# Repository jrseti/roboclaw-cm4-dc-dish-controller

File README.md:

# roboclaw-cm4-dc-dish-controller

A radio astronomy dish controller: a carrier board for a Raspberry Pi Compute
Module 4 (CM4) that commands a Basicmicro **RoboClaw 2x15A OEM** brushed DC motor
controller to drive the dish's azimuth and elevation motors. The board runs from a
12.8 V LiFePO4 battery that can be charged from a solar panel.

The goal is a self-contained observing system that points the dish, gathers data
and stores it for later retrieval and analysis. An SDR, such as an Airspy R2,
plugs into one USB port and an SSD into the other. The CM4 stores the samples
either raw or integrated. Both share one USB 2.0 link (about 35–40 MB/s), so raw
recording works at reduced bandwidth, such as the R2's 2.5 MSPS rate.

Data and control go through the CM4 over Ethernet. A battery-powered fiber media
converter can extend the link to the shack and isolate it electrically.

**Schematic:** [kicad/cm4-robo-controller.pdf](kicad/cm4-robo-controller.pdf)

**Simulations:** [sim/README.md](sim/README.md)

 **Tomachie Review:** [Tomachie AI](https://tomachie.com) reviewed the schematic. Here is the [review report](https://tomachie.com/r/17953055-d683-4b13-9460-e759b78ff8f2). Scored 100/100. Its other outputs are described in [tomachie/](tomachie/README.md).

**Power Integrity Report:** [KiPI](https://github.com/Tomachie/KiPI) simulated the power and ground copper of the layout. Here is the [power integrity report](kipi/cm4-robo-controller_kipi_report.pdf), with a summary in [kipi/](kipi/README.md).

## Overview

The board combines two modules:

- **Raspberry Pi CM4**: runs the pointing software and provides networking, USB,
  GPS timing and spare I/O. It plugs into two Hirose mezzanine connectors in the
  middle of the board.
- **RoboClaw 2x15A OEM**: a dual-channel controller for brushed DC motors (not
  brushless, stepper or servo) with closed-loop position and speed control. It
  plugs into two pin-header sockets on the right of the board. The CM4 sends it
  commands over a TTL serial link (RoboClaw packet serial).

The CM4 decides where the dish should point. The RoboClaw reads the axis sensors
and runs the motor control loops.

The functional diagram shows the board's layout: the CM4 on the left, the RoboClaw
on the right, and the field connections along the edges. Its source is
`drawings/FunctionalDiagram.drawio`.

## Motors and axis sensing

| Axis | Motor | Position sensor | RoboClaw input |
|---|---|---|---|
| Elevation (M1) | Firgelli F-SD-H-450-12V linear actuator (5.5 A max, 450 lb) | Built-in Hall sensors, quadrature A/B | EN1 (J8) |
| Azimuth (M2) | Bringsmart JGY-370 12 V worm-gear motor (1.8 A max) | AS5600 magnetic angle sensor, analog output | EN2 (J9) |

Both encoder channels are identical and jumper-configurable, so either axis can
use a quadrature encoder (the Firgelli Hall sensors, or an Omron E6B2-CWZ6C
open-collector encoder) or an absolute analog encoder (0–2 V at the RoboClaw).
Each 4-pin connector carries V+, A (or the analog signal), B and GND, with ESD
clamps on both signals.

| Jumper (ENC1 / ENC2) | Shunt | Setting |
|---|---|---|
| JP1 / JP4 — sensor supply (2x3, shunt across a row) | 1-2 | 5 V from the RoboClaw BEC (RC_5V) through F6 / F7, 200 mA PTC |
| | 3-4 | 3.3 V from the on-board LDO U18 (ENC_3V3) |
| | 5-6 | Battery voltage, 10–14.6 V (ENC_12V: V_MOTOR via a 350 mA PTC, SMAJ20A clamp), e.g. for an E6B2-CWZ6C |
| JP2 / JP5 — mode (2x3) | 1-3 + 2-4 | QUAD: A gets a 1k pull-up to 5 V and a 100R/10nF filter; B always does |
| | 3-5 + 4-6 | ABS: A goes to the analog node (100k/100nF); the pull-up is disconnected |
| JP3 / JP6 — ABS scaling | 1-2 | 68k/100k divider (×0.6) for a 3.3 V sensor such as the AS5600 |
| | 2-3 | 1k series, for a source that already outputs 0–2 V |

Default fit: ENC1 = 5 V, QUAD (Firgelli); ENC2 = 3.3 V, ABS, 3.3 V scaling (AS5600).

[docs/encoder-inputs.md](docs/encoder-inputs.md) explains, part by part, how the
channel handles each encoder type: the E6B2-CWZ6C's NPN open-collector outputs,
the Firgelli Hall quadrature, and an absolute 0–2 V encoder such as the AS5600.

| Elevation: Firgelli F-SD-H-450 linear actuator | Azimuth: Bringsmart JGY-370 worm-gear motor |
|:---:|:---:|
|  |  |

- **Elevation:** the actuator's Hall outputs (J8, JP2 in QUAD) are pulled up to
  the sensor supply (JP1 = 5 V), ESD-protected and RC-filtered before they reach
  EN1. The count is incremental, so the axis is homed at start-up.
- **Azimuth:** the AS5600 (J9, JP5 in ABS) gives an absolute angle as a 0–3.3 V
  signal. The 68k/100k divider (JP6 1-2) scales it to the RoboClaw's 0–2 V
  absolute-encoder input, so no homing is needed.
- **Switch inputs:** E-stop (J10 → S3), elevation limit (J12 → S4) and azimuth
  limit (J13 → S5). All use normally-closed switches and have ESD protection and
  filtering. The RoboClaw has one limit input per motor but supports two switches
  on it: wire the forward and reverse NC switches in series on J12/J13 (either
  one opening trips the input), set Invert, and set S4/S5 to *Limit (Both)* or
  *Home (User)/Limit (Fwd)* — the latter also zeroes the encoder against the
  reverse-end switch, which is how the elevation axis homes. All three switch
  loops run at battery voltage (ENC_12V, 4.7k pull-up, about 2.6 mA through the
  contacts for wetting on long cables) and a 47k/20k divider brings the
  open-switch 10–14.6 V down to 3.0–4.4 V at the RoboClaw pins.
- **Motor outputs:** J11 and J14, both 7.62 mm screw terminals.

The `Motor Notes` schematic sheet describes the sensor wiring and RoboClaw setup in
detail.

## Power

- **Input:** a 12.8 V, 12 Ah LiFePO4 battery (10.0–14.6 V) on J1, a 7.62 mm screw
  terminal. The battery is a GoldenMate CRIUS12, IP67 rated, and sits inside the
  enclosure. Its manual is in `docs/`.
- **Reverse-polarity protection:** a P-channel MOSFET (Q1) on the input blocks a
  battery connected backwards. It still conducts in both directions in normal use,
  so motor regenerative braking can return energy to the battery.
- **Fuses:** two ATO blade fuses split the supply:
  - F1 (15 A) feeds the RoboClaw motor supply (V_MOTOR).
  - F2 (5 A) feeds the logic branch.
  - D29 (SS54, 5 A Schottky, next to F1 above D1) sits across F1 as the return
    path for RoboClaw regenerative current when F1 is open, as the RoboClaw data
    sheet recommends. A fault that blows F1 pulls V_MOTOR low, so D29 cannot
    bypass the fuse.

  These are ordinary automotive blade fuses, the kind sold for car wiring. They are
  cheap and available almost anywhere. They plug into Keystone 3557-2 holders, so a
  blown fuse can be replaced in the field without tools. The board uses Littelfuse
  0287005.PXCN (5 A) and 0287015.PXCN (15 A), but any ATO/ATC fuse of the same
  rating fits.

  Q1 is the main protection against a reversed battery. A healthy Q1 blocks the
  reverse voltage, and no fuse should blow. The fuses are the backup. If Q1 has
  failed shorted, the reversed battery drives current forward through the input TVS diodes (D1, D3) and the
  RoboClaw's internal diodes. That current passes through F1 and F2, and the fuses
  are what stop it. A blown fuse after connecting the battery therefore means:
  check the polarity, and check Q1, before you fit a new fuse.

  The fuses do not cover every reverse fault. If board ground is also connected to
  the battery's negative terminal by another route, such as a USB device or other
  equipment that shares the battery, reverse current can flow through the ground
  wiring and bypass both Q1 and the fuses. 
- **Logic supply:** the logic branch goes through a hot-swap eFuse (U11), a power
  switch (SW1) and a 5 A buck converter (U15). The buck makes 5 V for the CM4 and the
  USB ports. The CM4's own 3.3 V output powers the 3.3 V logic.
- **SW1 is not a battery disconnect.** It switches the CM4 and logic supply only.
  With SW1 off the board still draws about 31 mA from the battery: about 30 mA for
  the RoboClaw's logic, which runs straight from V_MOTOR, plus about 1.3 mA for U11
  and its dividers. A full 12 Ah battery runs flat in about 16 days. For storage or
  transport, unplug J1 (or pull F1 and F2), and charge the battery first. A LiFePO4
  battery left at its BMS cutoff for months loses capacity.
- **Grounding:**
  - Motor return current stays on a separate ground (PGND). It joins the logic
    ground at a single point (NT1) next to the battery terminal.
  - Connector shields and mounting holes go to CHASSIS, which is bled to ground
    through 1 MΩ in parallel with 4.7 nF.
  - Once installed, GND is bonded to the utility box at the J2 antenna
    arrestor, the only intended GND-to-box connection. Battery negative
    already reaches the box through the board this way, so neither it nor
    the negative of anything else on the battery may have any other
    connection to the box or the mounting plate.
  - The optional FE-5680A rubidium reference (1PPS into J7) is mounted
    isolated from the plate and powered through an isolated DC-DC
    converter, so its only connection to the board is the J7 coax shield.
  - The SDR's antenna coax shield reaches board GND through its USB cable. Bring
    that coax in next to the J2 arrestor, or isolate its shield from the box, so
    it does not make a second GND-to-box bond.

## CM4 interfaces

- **Ethernet:** gigabit RJ45 with integrated magnetics. The PHY is on the CM4.
- **USB:**
  - A USB2514B hub drives a dual USB-A port, with current limiting and ESD
    protection. The hub's ports 3 and 4 are not used and are disabled by strap.
  - A USB mux switches the CM4's USB port to the USB-C connector for `rpiboot`
    (OTG programming of the eMMC).
- **GPS:**
  - A u-blox MAX-M10S receiver provides UTC time and a 1PPS pulse. Its antenna
    connects to an SMA jack, and a coin cell backs up the receiver for fast restarts.
  - A second SMA input accepts an external 1PPS reference, such as an FE-5680A
    rubidium clock.
- **GPIO header (J4):** spare CM4 GPIOs and two protected analog inputs. The
  3.3 V on pin 5 is fused at 100 mA (F9); the 5 V on pin 7 is not.
  Two on-axis E6B2-CWZ6C encoders can be read here, see
  [On-axis encoders on J4](docs/encoder-inputs.md#on-axis-encoders-on-j4-cm4).
  H7, an M2.5 hole next to J4, secures a plug-on HAT board; see
  [Mounting a HAT board on J4](docs/encoder-inputs.md#mounting-a-hat-board-on-j4).
- **Jumpers:** boot control, EEPROM write protect and self power-cycle.
- **Boot console UART (J5):** a serial console on the CM4's UART0. See below.

### Boot console UART (J5)

J5 is a 3-pin, 2.54 mm header that brings out the CM4's UART0. It shows bootloader
and Linux boot messages and gives a login prompt. That makes it the way into the
board when the network is down or the CM4 won't boot.

| J5 pin | Signal | Connect to the adapter's |
|---|---|---|
| 1 | BOOT_CONSOLE_RXD (GPIO15, CM4 receives) | TXD |
| 2 | BOOT_CONSOLE_TXD (GPIO14, CM4 transmits) | RXD |
| 3 | GND | GND |

TX and RX cross over: the adapter's TXD goes to the CM4's RXD.

Any inexpensive USB-to-TTL serial cable works. Cables like the one shown, based on
the PL2303, CP2102 or FTDI chips, cost a few dollars on Amazon. They usually have
four female jumper leads: black GND, white RXD, green TXD and red 5V. Check the
labels on your cable.

- **Do not connect the red 5V lead.** The board powers itself, and J5 has no 5 V
  pin. A loose 5 V lead can short against the header or the board, so it's best
  to cut it off, or at least insulate it.
- **Use a cable with 3.3 V signals.** The CM4's GPIOs are not 5 V tolerant. Before
  connecting, check with a meter that the adapter's TXD idles at about 3.3 V.
- **Settings:** 115200 baud, 8N1, no flow control.
- **Enabling the console:**
  - For the Linux console, add `enable_uart=1` to `config.txt`. Raspberry Pi OS
    already puts `console=serial0,115200` in `cmdline.txt`.
  - For bootloader messages, set `BOOT_UART=1` in the EEPROM config with
    `rpi-eeprom-config`.

### Recommended CM4

Use a **CM4 without wireless and with eMMC**, for example `CM4004032` (4 GB RAM,
32 GB eMMC) or `CM4004016` (16 GB eMMC).

- The board has no SD-card slot, so a CM4 Lite (part numbers ending `000`) cannot
  boot on it.
- On a wireless CM4, Bluetooth takes UART0, which this board uses.

## Board

- 4-layer PCB, 150 × 90 mm, with four M3 mounting holes.
- Assembled on one side by JLCPCB. Parts carry LCSC part numbers. The RoboClaw
  (A1) and the CM4 (A2) are DNP: bought separately and fitted by hand. The two
  Hirose DF40 receptacles under the CM4 are J17/J18, BOM and placement entries
  only, since their pads are part of the CM4 footprint.
- The RoboClaw sits in sockets (J15/J16) so it can be removed. Nothing is placed
  under the CM4 or the RoboClaw.
- The inner layers are planes:
  - In1.Cu is ground, split into logic GND and PGND.
  - In2.Cu carries power: +5 V on the logic side, V_MOTOR on the RoboClaw side.

## Status

The schematic is complete. PCB placement and plane layout are done, and routing is
in progress. The software has not been started yet.

## Repository layout

| Path | Contents |
|---|---|
| `kicad/` | KiCad 10 project: schematic sheets and PCB |
| `parts/` | Git submodule ([jrseti/parts](https://github.com/jrseti/parts)): the `MyParts` symbol, footprint and 3D-model library, its datasheets, and `add.py` for importing LCSC parts |
| `docs/` | Component datasheets and design notes |
| `drawings/` | Draw.io source for the functional diagram |
| `tomachie/` | Tomachie schematic review: report PDF, BOM, netlist, power tree and marked-up sheets ([README](tomachie/README.md)) |
| `kipi/` | KiPI power integrity report for the layout: voltage drop, current density, via currents and copper temperature ([README](kipi/README.md)) |
| `images/` | Images used in this README |
| `software/` | CM4 software (not yet started) |

### Cloning

`parts/` is a submodule, and the KiCad project needs it to find its symbols,
footprints and 3D models. Clone with:

```sh
git clone --recurse-submodules https://github.com/jrseti/roboclaw-cm4-dc-dish-controller.git
```

If you have already cloned the repository, run `git submodule update --init` to
fetch it.

KiCad finds the library through two path variables. Set them in
**Preferences → Configure Paths**:

| Variable | Value |
|---|---|
| `MYPARTS` | `<clone>/parts` |
| `MYPARTS_DATASHEETS` | `<clone>/parts/datasheets` |

## License

MIT. See [LICENSE](LICENSE).

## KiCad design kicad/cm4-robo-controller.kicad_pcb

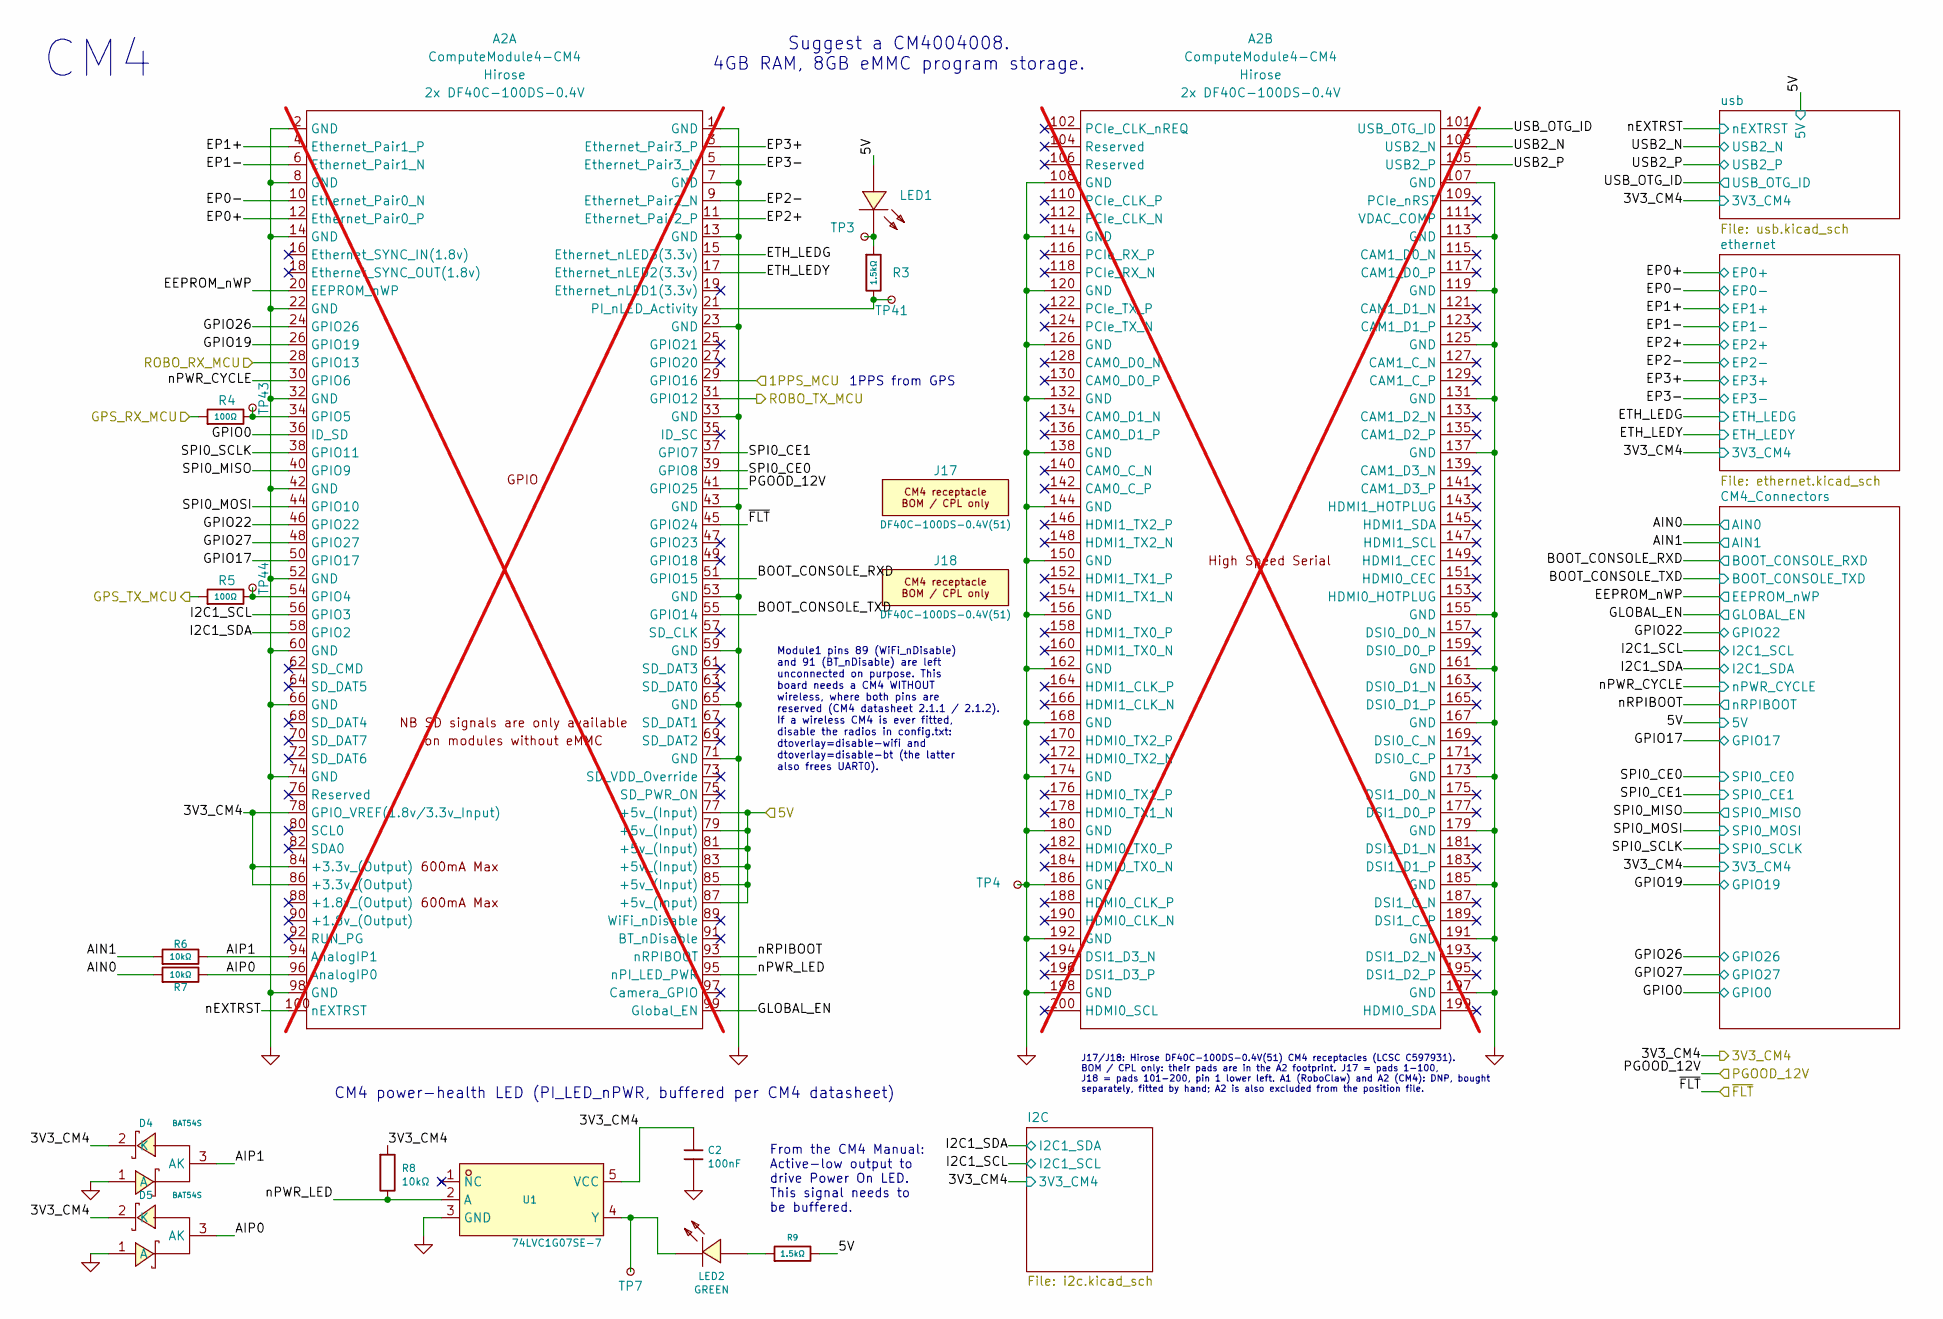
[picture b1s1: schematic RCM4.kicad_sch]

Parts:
A2: ComputeModule4-CM4; Raspberry-Pi-4-Compute-Module; MPN CM4004008; not fitted
C2: 100nF; CAPC1005X55N; Tolerance ±10%; Voltage Rating 16V; MPN CL05B104KO5NNNC; LCSC Part C1525
D4, D5: BAT54S; SOT95P280X110-3N; MPN BAT54S,215; LCSC Part C47546
J17, J18: DF40C-100DS-0.4V(51); DF40C-100DS-0.4V_BOM-ONLY; MPN DF40C-100DS-0.4V(51); LCSC Part C597931
LED1: GREEN; LEDC2012X110N; MPN KT-0805G; LCSC Part C2297
LED2: GREEN; LEDC2012X110N; MPN KT-0805R; LCSC Part C2295
R3, R9: 1.5kΩ; RESC1005X40N; Tolerance ±1%; Voltage Rating 50V; MPN 0402WGF1501TCE; LCSC Part C25867
R4, R5: 100Ω; RESC1005X40N; Tolerance ±1%; Voltage Rating 50V; MPN 0402WGF1000TCE; LCSC Part C25076
R6, R7, R8: 10kΩ; RESC1005X40N; Tolerance ±1%; Voltage Rating 50V; MPN 0402WGF1002TCE; LCSC Part C25744
TP3, TP4, TP7, TP41, TP43, TP44: TestPoint_Small; TestPoint_Pad_D0.8mm
U1: 74LVC1G07SE-7; SOT65P210X110-5N; MPN 74LVC1G07SE-7; LCSC Part C67531

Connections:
/3V3_CM4: A2.78 (GPIO_VREF(1.8v/3.3v_Input)), A2.84 (+3.3v_(Output)), A2.86 (+3.3v_(Output)), C2.1, D4.2 (K), D5.2 (K), R8.1, U1.5 (VCC); also elsewhere on the board
/5V: A2.77 (+5v_(Input)), A2.79 (+5v_(Input)), A2.81 (+5v_(Input)), A2.83 (+5v_(Input)), A2.85 (+5v_(Input)), A2.87 (+5v_(Input)), LED1.1 (A), R9.2; also elsewhere on the board
/CM4/1PPS_MCU: A2.29 (GPIO16); also elsewhere on the board
/CM4/AIN0: R7.1; also elsewhere on the board
/CM4/AIN1: R6.1; also elsewhere on the board
/CM4/AIP0: A2.96 (AnalogIP0), D5.3 (AK), R7.2
/CM4/AIP1: A2.94 (AnalogIP1), D4.3 (AK), R6.2
/CM4/BOOT_CONSOLE_RXD: A2.51 (GPIO15); also elsewhere on the board
/CM4/BOOT_CONSOLE_TXD: A2.55 (GPIO14); also elsewhere on the board
/CM4/EEPROM_nWP: A2.20 (EEPROM_nWP); also elsewhere on the board
/CM4/EP0+: A2.12 (Ethernet_Pair0_P); also elsewhere on the board
/CM4/EP0-: A2.10 (Ethernet_Pair0_N); also elsewhere on the board
/CM4/EP1+: A2.4 (Ethernet_Pair1_P); also elsewhere on the board
/CM4/EP1-: A2.6 (Ethernet_Pair1_N); also elsewhere on the board
/CM4/EP2+: A2.11 (Ethernet_Pair2_P); also elsewhere on the board
/CM4/EP2-: A2.9 (Ethernet_Pair2_N); also elsewhere on the board
/CM4/EP3+: A2.3 (Ethernet_Pair3_P); also elsewhere on the board
/CM4/EP3-: A2.5 (Ethernet_Pair3_N); also elsewhere on the board
/CM4/ETH_LEDG: A2.15 (Ethernet_nLED3(3.3v)); also elsewhere on the board
/CM4/ETH_LEDY: A2.17 (Ethernet_nLED2(3.3v)); also elsewhere on the board
/CM4/GLOBAL_EN: A2.99 (Global_EN); also elsewhere on the board
/CM4/GPIO0: A2.36 (ID_SD); also elsewhere on the board
/CM4/GPIO17: A2.50 (GPIO17); also elsewhere on the board
/CM4/GPIO19: A2.26 (GPIO19); also elsewhere on the board
/CM4/GPIO22: A2.46 (GPIO22); also elsewhere on the board
/CM4/GPIO26: A2.24 (GPIO26); also elsewhere on the board
/CM4/GPIO27: A2.48 (GPIO27); also elsewhere on the board
/CM4/GPS_RX_MCU: R4.1; also elsewhere on the board
/CM4/GPS_TX_MCU: R5.1; also elsewhere on the board
/CM4/I2C1_SCL: A2.56 (GPIO3); also elsewhere on the board
/CM4/I2C1_SDA: A2.58 (GPIO2); also elsewhere on the board
/CM4/PGOOD_12V: A2.41 (GPIO25); also elsewhere on the board
/CM4/ROBO_RX_MCU: A2.28 (GPIO13); also elsewhere on the board
/CM4/ROBO_TX_MCU: A2.31 (GPIO12); also elsewhere on the board
/CM4/SPI0_CE0: A2.39 (GPIO8); also elsewhere on the board
/CM4/SPI0_CE1: A2.37 (GPIO7); also elsewhere on the board
/CM4/SPI0_MISO: A2.40 (GPIO9); also elsewhere on the board
/CM4/SPI0_MOSI: A2.44 (GPIO10); also elsewhere on the board
/CM4/SPI0_SCLK: A2.38 (GPIO11); also elsewhere on the board
/CM4/USB2_N: A2.103 (USB2_N); also elsewhere on the board
/CM4/USB2_P: A2.105 (USB2_P); also elsewhere on the board
/CM4/USB_OTG_ID: A2.101 (USB_OTG_ID); also elsewhere on the board
/CM4/nEXTRST: A2.100 (nEXTRST); also elsewhere on the board
/CM4/nPWR_CYCLE: A2.30 (GPIO6); also elsewhere on the board
/CM4/nPWR_LED: A2.95 (nPI_LED_PWR), R8.2, U1.2 (A)
/CM4/nRPIBOOT: A2.93 (nRPIBOOT); also elsewhere on the board
/CM4/~FLT: A2.45 (GPIO24); also elsewhere on the board
GND: A2.1 (GND), A2.2 (GND), A2.7 (GND), A2.8 (GND), A2.13 (GND), A2.14 (GND), A2.22 (GND), A2.23 (GND), A2.32 (GND), A2.33 (GND), A2.42 (GND), A2.43 (GND), A2.52 (GND), A2.53 (GND), A2.59 (GND), A2.60 (GND), A2.65 (GND), A2.66 (GND), A2.71 (GND), A2.74 (GND), A2.98 (GND), A2.107 (GND), A2.108 (GND), A2.113 (GND), A2.114 (GND), A2.119 (GND), A2.120 (GND), A2.125 (GND), A2.126 (GND), A2.131 (GND), A2.132 (GND), A2.137 (GND), A2.138 (GND), A2.144 (GND), A2.150 (GND), A2.155 (GND), A2.156 (GND), A2.161 (GND), A2.162 (GND), A2.167 (GND), A2.168 (GND), A2.173 (GND), A2.174 (GND), A2.179 (GND), A2.180 (GND), A2.185 (GND), A2.186 (GND), A2.191 (GND), A2.192 (GND), A2.197 (GND), A2.198 (GND), C2.2, D4.1 (A), D5.1 (A), TP4.1 (1_1), U1.3 (GND); also elsewhere on the board
unnamed: A2.54 (GPIO4), R5.2, TP44.1 (1_1)
unnamed: A2.34 (GPIO5), R4.2, TP43.1 (1_1)
unnamed: A2.21 (PI_nLED_Activity), R3.2, TP41.1 (1_1)
unnamed: LED1.2 (K), R3.1, TP3.1 (1_1)
unnamed: LED2.1 (A), R9.1
unnamed: LED2.2 (K), TP7.1 (1_1), U1.4 (Y)

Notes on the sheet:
CM4 power-health LED (PI_LED_nPWR, buffered per CM4 datasheet)
J17/J18: Hirose DF40C-100DS-0.4V(51) CM4 receptacles (LCSC C597931). BOM / CPL only: their pads are in the A2 footprint. J17 = pads 1-100, J18 = pads 101-200, pin 1 lower left. A1 (RoboClaw) and A2 (CM4): DNP, bought separately, fitted by hand; A2 is also excluded from the position file.
Module1 pins 89 (WiFi_nDisable) and 91 (BT_nDisable) are left unconnected on purpose. This board needs a CM4 WITHOUT wireless, where both pins are reserved (CM4 datasheet 2.1.1 / 2.1.2). If a wireless CM4 is ever fitted, disable the radios in config.txt: dtoverlay=disable-wifi and dtoverlay=disable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
CM4
Suggest a CM4004008. 4GB RAM, 8GB eMMC program storage.
From the CM4 Manual: Active-low output to drive Power On LED. This signal needs to be buffered.
1PPS from GPS

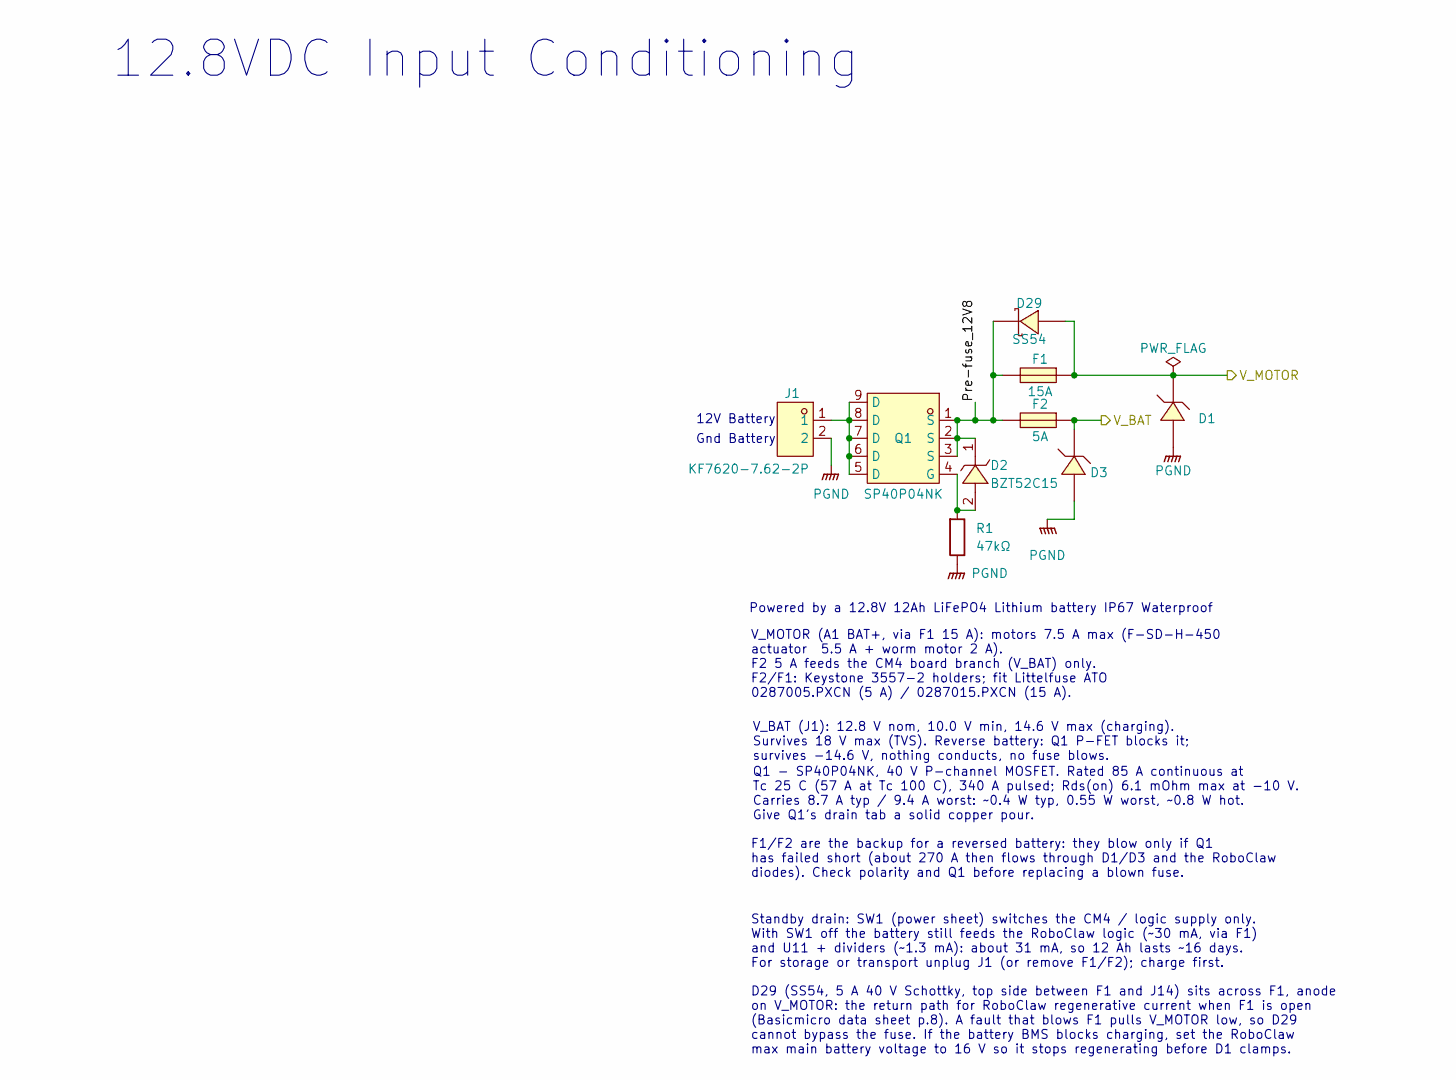
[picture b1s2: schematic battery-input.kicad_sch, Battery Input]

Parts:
D1, D3: SMCJ18A_C53260906; DIOM7959X262N; MPN SMCJ18A; LCSC Part C53260906
D2: BZT52C15; SOD3716X135N; MPN BZT52C15; LCSC Part C19077412
D29: SS54; DIOM5226X244N; MPN SS54; LCSC Part C22452
F1: 15A; FUSE-TH_4P-L19.8-W6.7_3557-2; Voltage Rating 32VDC; Interrupting Rating 1000A @ 32VDC; MPN 3557-2; LCSC Part C352820
F2: 5A; FUSE-TH_4P-L19.8-W6.7_3557-2; Voltage Rating 32VDC; Interrupting Rating 1000A @ 32VDC; MPN 3557-2; LCSC Part C352820
J1: KF7620-7.62-2P; CONN-TH_P7.62_KF7620-7.62-2P; MPN KF7620-7.62-2P; LCSC Part C475104
Q1: SP40P04NK; SON127P600X500X110-9N; MPN SP40P04NK; LCSC Part C41355035
R1: 47kΩ; RESC1005X40N; Tolerance ±1%; Voltage Rating 50V; MPN 0402WGF4702TCE; LCSC Part C25792

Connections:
/Robo/V_MOTOR: D1.1 (C), D29.2 (A), F1.1, F1.2; also elsewhere on the board
/battery-input/Pre-fuse_12V8: D2.1 (K), D29.1 (K), F1.3, F1.4, F2.3, F2.4, Q1.1 (S), Q1.2 (S), Q1.3 (S)
/battery-input/V_BAT: D3.1 (C), F2.1, F2.2; also elsewhere on the board
unnamed: D2.2 (A), Q1.4 (G), R1.1
unnamed: J1.1, Q1.5 (D), Q1.6 (D), Q1.7 (D), Q1.8 (D), Q1.9 (D)
PGND: D1.2 (A), D3.2 (A), J1.2, R1.2; also elsewhere on the board

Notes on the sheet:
Gnd Battery
12.8VDC Input Conditioning
V_MOTOR (A1 BAT+, via F1 15 A): motors 7.5 A max (F-SD-H-450 actuator 5.5 A + worm motor 2 A). F2 5 A feeds the CM4 board branch (V_BAT) only. F2/F1: Keystone 3557-2 holders; fit Littelfuse ATO 0287005.PXCN (5 A) / 0287015.PXCN (15 A).
12V Battery
D29 (SS54, 5 A 40 V Schottky, top side between F1 and J14) sits across F1, anode on V_MOTOR: the return path for RoboClaw regenerative current when F1 is open (Basicmicro data sheet p.8). A fault that blows F1 pulls V_MOTOR low, so D29 cannot bypass the fuse. If the battery BMS blocks charging, set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
Standby drain: SW1 (power sheet) switches the CM4 / logic supply only. With SW1 off the battery still feeds the RoboClaw logic (~30 mA, via F1) and U11 + dividers (~1.3 mA): about 31 mA, so 12 Ah lasts ~16 days. For storage or transport unplug J1 (or remove F1/F2); charge first.
V_BAT (J1): 12.8 V nom, 10.0 V min, 14.6 V max (charging). Survives 18 V max (TVS). Reverse battery: Q1 P-FET blocks it; survives -14.6 V, nothing conducts, no fuse blows.
F1/F2 are the backup for a reversed battery: they blow only if Q1 has failed short (about 270 A then flows through D1/D3 and the RoboClaw diodes). Check polarity and Q1 before replacing a blown fuse.
Powered by a 12.8V 12Ah LiFePO4 Lithium battery IP67 Waterproof
Q1 - SP40P04NK, 40 V P-channel MOSFET. Rated 85 A continuous at Tc 25 C (57 A at Tc 100 C), 340 A pulsed; Rds(on) 6.1 mOhm max at -10 V. Carries 8.7 A typ / 9.4 A worst: ~0.4 W typ, 0.55 W worst, ~0.8 W hot. Give Q1's drain tab a solid copper pour.

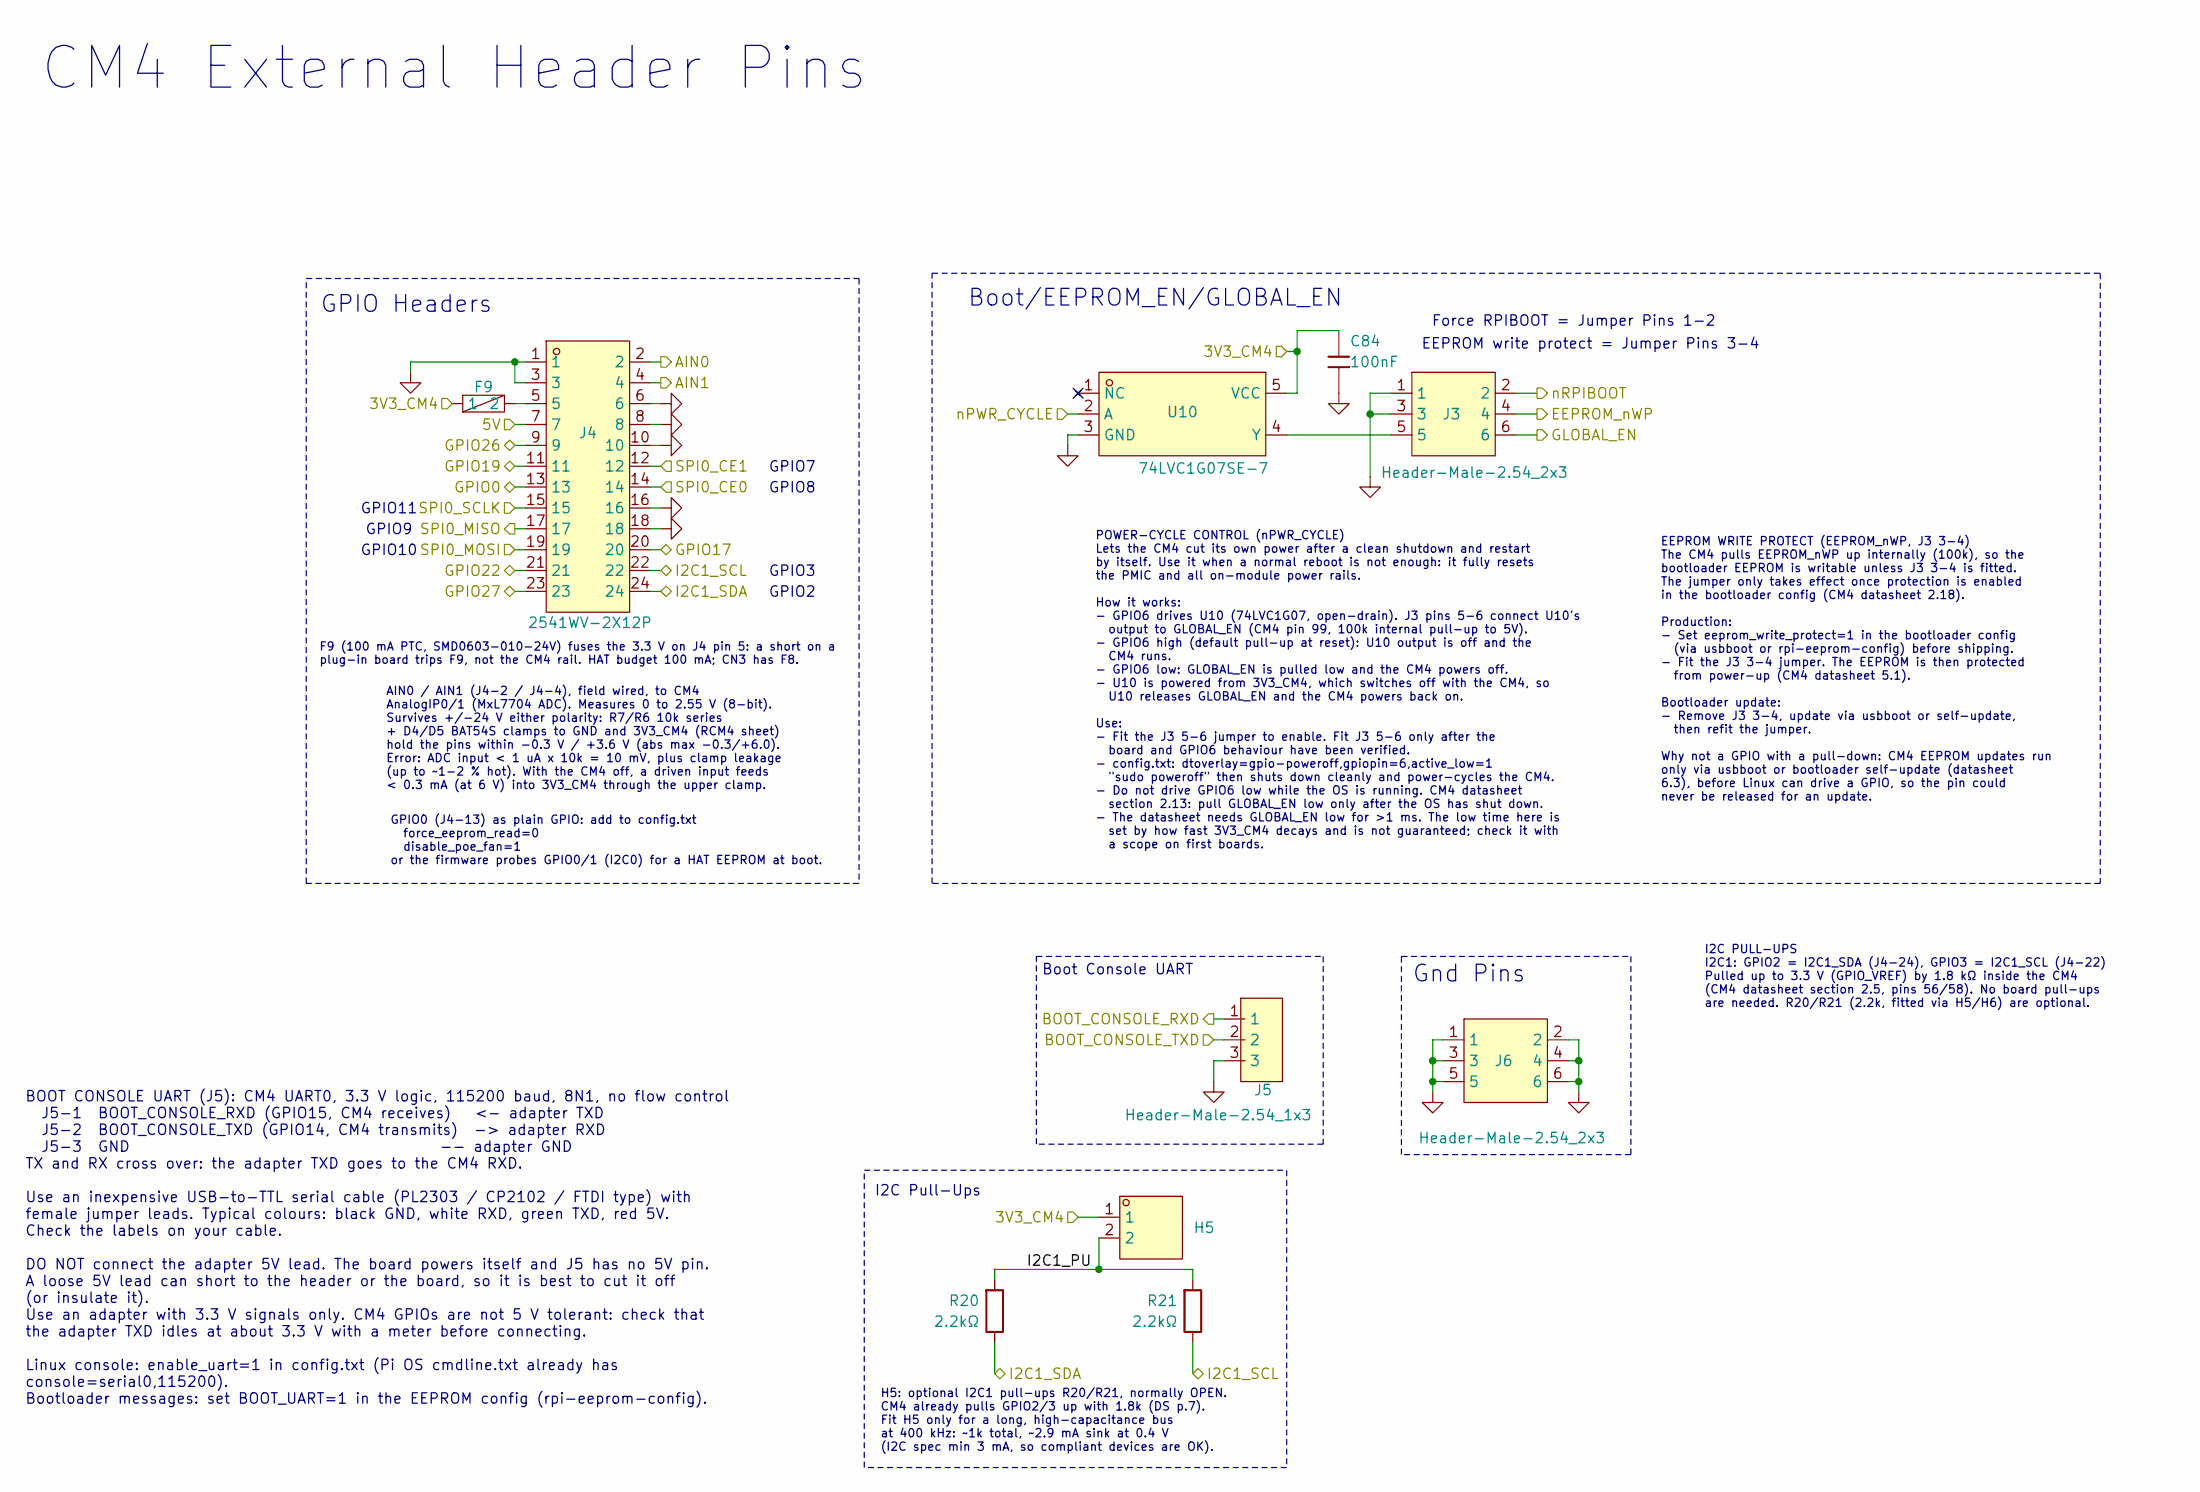
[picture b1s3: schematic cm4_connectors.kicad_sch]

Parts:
C84: 100nF; CAPC1005X55N; Tolerance ±10%; Voltage Rating 16V; MPN CL05B104KO5NNNC; LCSC Part C1525
F9: 100mA; FUSC1608X100N; MPN SMD0603-010-24V; LCSC Part C70048
H5: 210S-1*2P L=11.6MMGold-plated black; HDR-TH_2P-P2.54-V-M-1; MPN B-2100S02P-A110; LCSC Part C124375
J3, J6: Header-Male-2.54_2x3; HDR-TH_6P-P2.54-V-M-R2-C3-S2.54-1; MPN 2.54-2*3PPin; LCSC Part C65114
J4: 2541WV-2X12P; HDR-TH_24P-P2.54-V-M-R2-C12-S2.54; MPN 2541WV-2x12P; LCSC Part C5383110
J5: Header-Male-2.54_1x3; HDR-TH_3P-P2.54-V-M-1; MPN 2.54-1*3PPin; LCSC Part C49257
R20, R21: 2.2kΩ; RESC1005X40N; Tolerance ±1%; Voltage Rating 50V; MPN 0402WGF2201TCE; LCSC Part C25879
U10: 74LVC1G07SE-7; SOT65P210X110-5N; MPN 74LVC1G07SE-7; LCSC Part C67531

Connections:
/3V3_CM4: C84.1, F9.1, H5.1, U10.5 (VCC); also elsewhere on the board
/5V: J4.7; also elsewhere on the board
/CM4/AIN0: J4.2; also elsewhere on the board
/CM4/AIN1: J4.4; also elsewhere on the board
/CM4/BOOT_CONSOLE_RXD: J5.1; also elsewhere on the board
/CM4/BOOT_CONSOLE_TXD: J5.2; also elsewhere on the board
/CM4/CM4_Connectors/I2C1_PU: H5.2, R20.1, R21.1
/CM4/EEPROM_nWP: J3.4; also elsewhere on the board
/CM4/GLOBAL_EN: J3.6; also elsewhere on the board
/CM4/GPIO0: J4.13; also elsewhere on the board
/CM4/GPIO17: J4.20; also elsewhere on the board
/CM4/GPIO19: J4.11; also elsewhere on the board
/CM4/GPIO22: J4.21; also elsewhere on the board
/CM4/GPIO26: J4.9; also elsewhere on the board
/CM4/GPIO27: J4.23; also elsewhere on the board
/CM4/I2C1_SCL: J4.22, R21.2; also elsewhere on the board
/CM4/I2C1_SDA: J4.24, R20.2; also elsewhere on the board
/CM4/SPI0_CE0: J4.14; also elsewhere on the board
/CM4/SPI0_CE1: J4.12; also elsewhere on the board
/CM4/SPI0_MISO: J4.17; also elsewhere on the board
/CM4/SPI0_MOSI: J4.19; also elsewhere on the board
/CM4/SPI0_SCLK: J4.15; also elsewhere on the board
/CM4/nPWR_CYCLE: U10.2 (A); also elsewhere on the board
/CM4/nRPIBOOT: J3.2; also elsewhere on the board
GND: C84.2, J3.1, J3.3, J4.1, J4.3, J4.6, J4.8, J4.10, J4.16, J4.18, J5.3, J6.1, J6.2, J6.3, J6.4, J6.5, J6.6, U10.3 (GND); also elsewhere on the board
unnamed: F9.2, J4.5
unnamed: J3.5, U10.4 (Y)

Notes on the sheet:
Boot Console UART
I2C Pull-Ups
GPIO2
GPIO0 (J4-13) as plain GPIO: add to config.txt force_eeprom_read=0 disable_poe_fan=1 or the firmware probes GPIO0/1 (I2C0) for a HAT EEPROM at boot.
EEPROM WRITE PROTECT (EEPROM_nWP, J3 3-4) The CM4 pulls EEPROM_nWP up internally (100k), so the bootloader EEPROM is writable unless J3 3-4 is fitted. The jumper only takes effect once protection is enabled in the bootloader config (CM4 datasheet 2.18). Production: - Set eeprom_write_protect=1 in t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
H5: optional I2C1 pull-ups R20/R21, normally OPEN. CM4 already pulls GPIO2/3 up with 1.8k (DS p.7). Fit H5 only for a long, high-capacitance bus at 400 kHz: ~1k total, ~2.9 mA sink at 0.4 V (I2C spec min 3 mA, so compliant devices are OK).
I2C PULL-UPS I2C1: GPIO2 = I2C1_SDA (J4-24), GPIO3 = I2C1_SCL (J4-22) Pulled up to 3.3 V (GPIO_VREF) by 1.8 kΩ inside the CM4 (CM4 datasheet section 2.5, pins 56/58). No board pull-ups are needed. R20/R21 (2.2k, fitted via H5/H6) are optional.
EEPROM write protect = Jumper Pins 3-4
GPIO3
BOOT CONSOLE UART (J5): CM4 UART0, 3.3 V logic, 115200 baud, 8N1, no flow control J5-1 BOOT_CONSOLE_RXD (GPIO15, CM4 receives) <- adapter TXD J5-2 BOOT_CONSOLE_TXD (GPIO14, CM4 transmits) -> adapter RXD J5-3 GND -- adapter GND TX and RX cross over: the adapter TXD goes to the CM4 RXD. Use an inexpe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
AIN0 / AIN1 (J4-2 / J4-4), field wired, to CM4 AnalogIP0/1 (MxL7704 ADC). Measures 0 to 2.55 V (8-bit). Survives +/-24 V either polarity: R7/R6 10k series + D4/D5 BAT54S clamps to GND and 3V3_CM4 (RCM4 sheet) hold the pins within -0.3 V / +3.6 V (abs max -0.3/+6.0). Error: ADC input < 1 uA x 10k = 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
CM4 External Header Pins
GPIO9
GPIO10
Gnd Pins
Boot/EEPROM_EN/GLOBAL_EN
POWER-CYCLE CONTROL (nPWR_CYCLE) Lets the CM4 cut its own power after a clean shutdown and restart by itself. Use it when a normal reboot is not enough: it fully resets the PMIC and all on-module power rails. How it works: - GPIO6 drives U10 (74LVC1G07, open-drain). J3 pins 5-6 connect U10's output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
GPIO8
GPIO7
Force RPIBOOT = Jumper Pins 1-2
F9 (100 mA PTC, SMD0603-010-24V) fuses the 3.3 V on J4 pin 5: a short on a plug-in board trips F9, not the CM4 rail. HAT budget 100 mA; CN3 has F8.
GPIO Headers
GPIO11

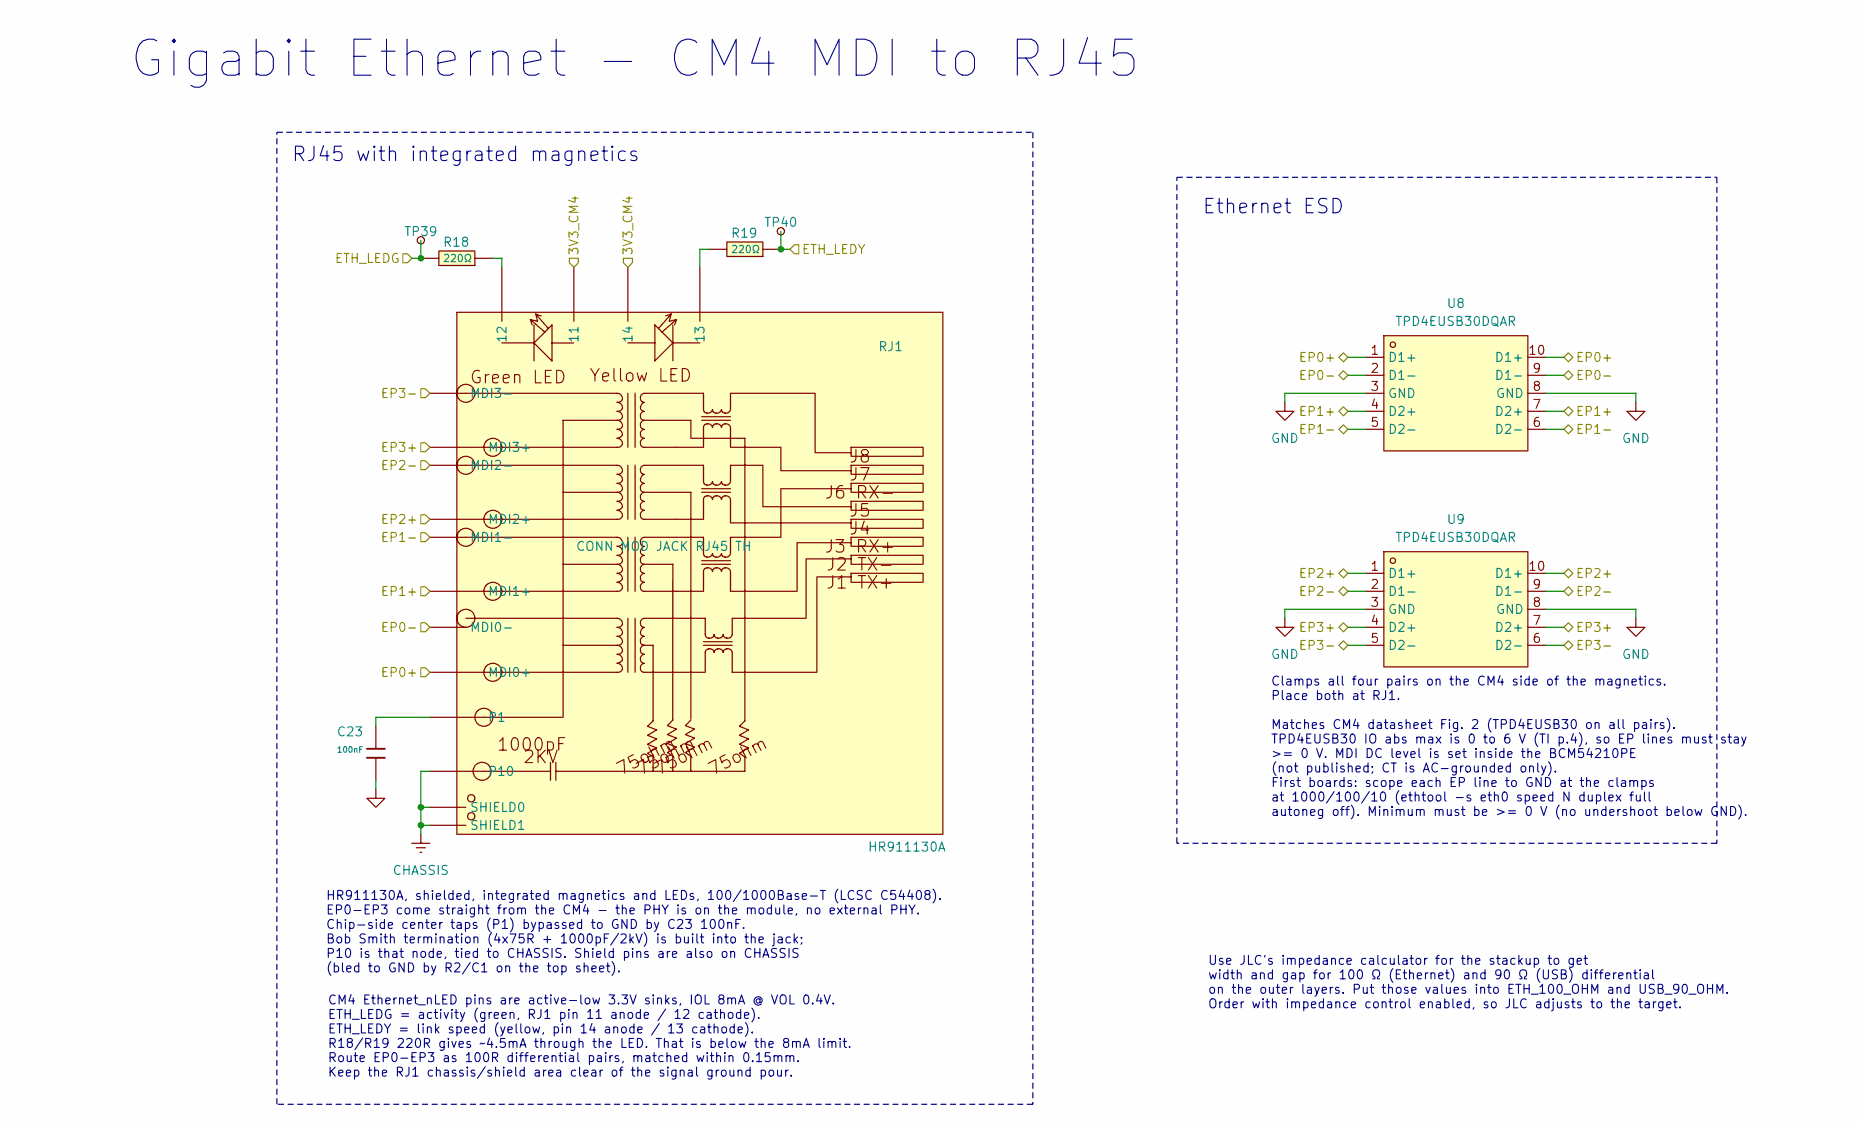
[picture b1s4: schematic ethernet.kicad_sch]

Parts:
C23: 100nF; CAPC1005X55N; Tolerance ±10%; Voltage Rating 16V; MPN CL05B104KO5NNNC; LCSC Part C1525
R18, R19: 220Ω; RESC1005X40N; Tolerance ±1%; Voltage Rating 50V; MPN 0402WGF2200TCE; LCSC Part C25091
RJ1: HR911130A; RJ45-TH_HR911130A; MPN HR911130A; LCSC Part C54408
TP39, TP40: TestPoint_Small; TestPoint_Pad_D0.8mm
U8, U9: TPD4EUSB30DQAR; SON50P100X250X60-10N; MPN TPD4EUSB30DQAR; LCSC Part C90627

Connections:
/3V3_CM4: RJ1.11, RJ1.14; also elsewhere on the board
/CM4/EP0+: RJ1.P2 (MDI0+), U8.1 (D1+), U8.10 (D1+); also elsewhere on the board
/CM4/EP0-: RJ1.P3 (MDI0-), U8.2 (D1-), U8.9 (D1-); also elsewhere on the board
/CM4/EP1+: RJ1.P4 (MDI1+), U8.4 (D2+), U8.7 (D2+); also elsewhere on the board
/CM4/EP1-: RJ1.P7 (MDI1-), U8.5 (D2-), U8.6 (D2-); also elsewhere on the board
/CM4/EP2+: RJ1.P5 (MDI2+), U9.1 (D1+), U9.10 (D1+); also elsewhere on the board
/CM4/EP2-: RJ1.P6 (MDI2-), U9.2 (D1-), U9.9 (D1-); also elsewhere on the board
/CM4/EP3+: RJ1.P8 (MDI3+), U9.4 (D2+), U9.7 (D2+); also elsewhere on the board
/CM4/EP3-: RJ1.P9 (MDI3-), U9.5 (D2-), U9.6 (D2-); also elsewhere on the board
/CM4/ETH_LEDG: R18.2, TP39.1 (1_1); also elsewhere on the board
/CM4/ETH_LEDY: R19.1, TP40.1 (1_1); also elsewhere on the board
CHASSIS: RJ1.P10, RJ1.SHIELD0, RJ1.SHIELD1; also elsewhere on the board
GND: C23.2, U8.3 (GND), U8.8 (GND), U9.3 (GND), U9.8 (GND); also elsewhere on the board
unnamed: C23.1, RJ1.P1
unnamed: R18.1, RJ1.12
unnamed: R19.2, RJ1.13

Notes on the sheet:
Ethernet ESD
Use JLC's impedance calculator for the stackup to get width and gap for 100 Ω (Ethernet) and 90 Ω (USB) differential on the outer layers. Put those values into ETH_100_OHM and USB_90_OHM. Order with impedance control enabled, so JLC adjusts to the target.
HR911130A, shielded, integrated magnetics and LEDs, 100/1000Base-T (LCSC C54408). EP0-EP3 come straight from the CM4 - the PHY is on the module, no external PHY. Chip-side center taps (P1) bypassed to GND by C23 100nF. Bob Smith termination (4x75R + 1000pF/2kV) is built into the jack; P10 is that n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
RJ45 with integrated magnetics
Clamps all four pairs on the CM4 side of the magnetics. Place both at RJ1. Matches CM4 datasheet Fig. 2 (TPD4EUSB30 on all pairs). TPD4EUSB30 IO abs max is 0 to 6 V (TI p.4), so EP lines must stay >= 0 V. MDI DC level is set inside the BCM54210PE (not published; CT is AC-grounded only). First board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
Route EP0-EP3 as 100R differential pairs, matched within 0.15mm. Keep the RJ1 chassis/shield area clear of the signal ground pour.
CM4 Ethernet_nLED pins are active-low 3.3V sinks, IOL 8mA @ VOL 0.4V. ETH_LEDG = activity (green, RJ1 pin 11 anode / 12 cathode). ETH_LEDY = link speed (yellow, pin 14 anode / 13 cathode). R18/R19 220R gives ~4.5mA through the LED. That is below the 8mA limit.
Gigabit Ethernet - CM4 MDI to RJ45
